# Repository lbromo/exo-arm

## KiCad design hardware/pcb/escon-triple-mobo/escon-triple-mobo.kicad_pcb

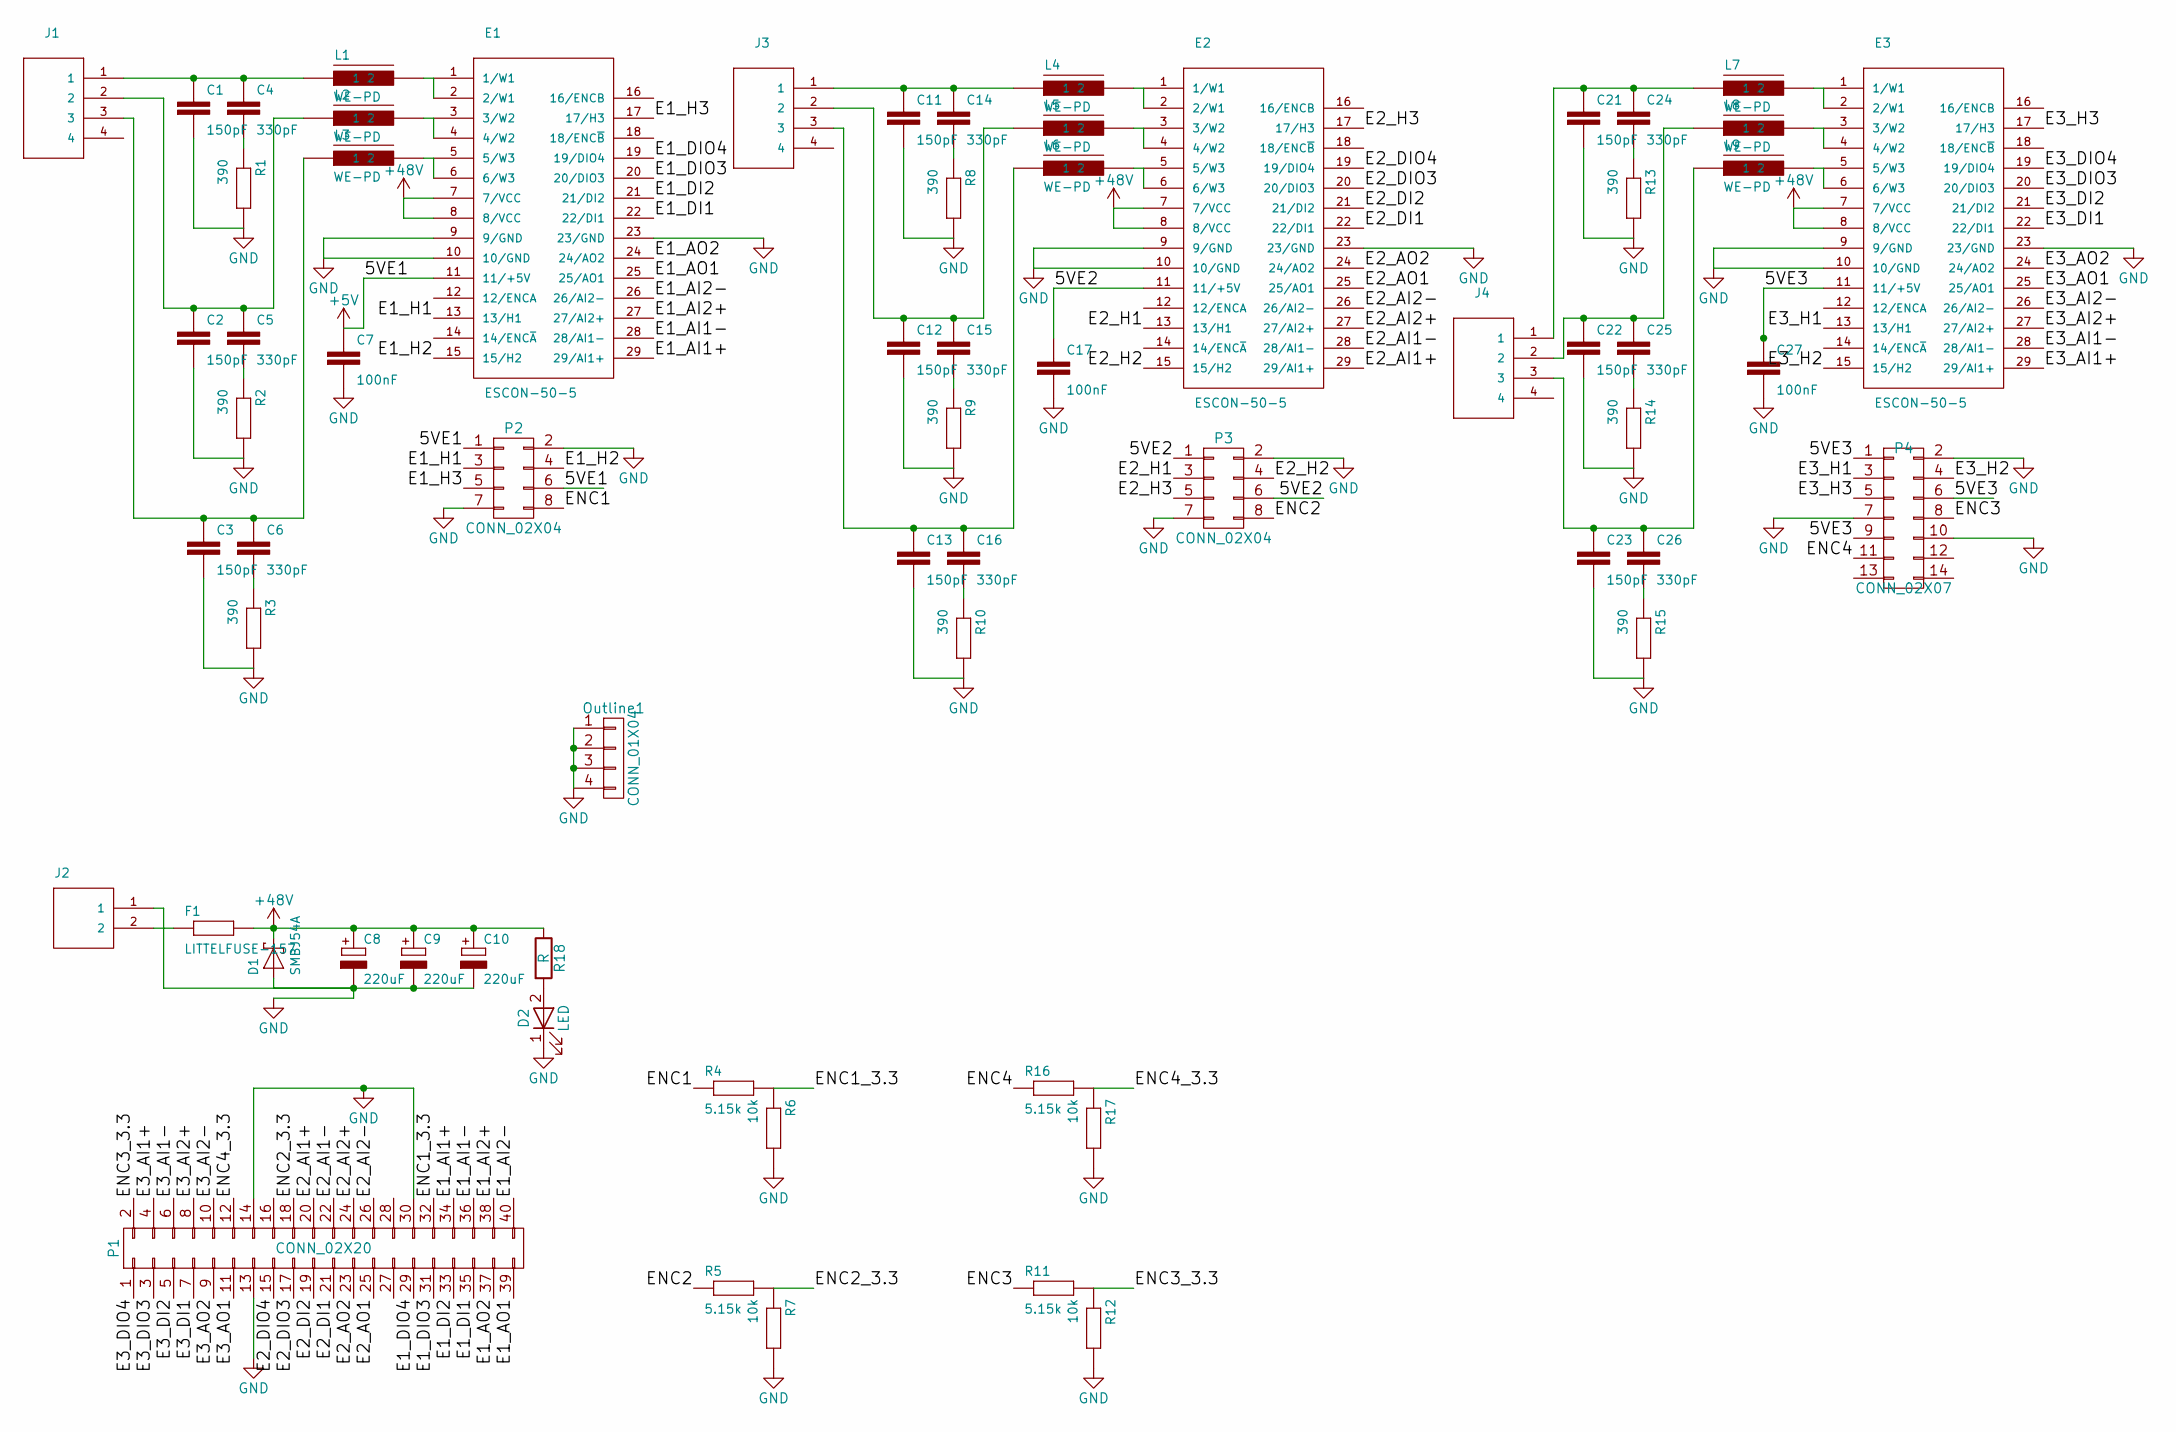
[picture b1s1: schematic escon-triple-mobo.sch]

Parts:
C1, C2, C3, C11, C12, C13, C21, C22, C23: 150pF; C_0805_HandSoldering
C4, C5, C6, C14, C15, C16, C24, C25, C26: 330pF; C_0805_HandSoldering
C7, C17, C27: 100nF; C_0805_HandSoldering
C8, C9, C10: 220uF; electrolyte-12-5
D1: SMBJ54A; SMB_Handsoldering
D2: LED; LED_0805
E1, E2, E3: ESCON-50-5; escon-50-5
F1: LITTELFUSE-157; Luttelfuse-157
J1, J3, J4: PHOENIX-COMBICON-MCV-4POS; PhoenixContact_MCV-G_04x3.50mm_Vertical
J2: PHOENIX-COMBICON-MCV-2POS; PhoenixContact_MCV-G_02x3.50mm_Vertical
L1, L2, L3, L4, L5, L6, L7, L8, L9: WE-PD; WE22uH
Outline1: CONN_01X04; EuroBoard160mmX100mm_holes
P1: CONN_02X20; IDC_Header_Straight_40pins
P2, P3: CONN_02X04; IDC_Header_Straight_8pins
P4: CONN_02X07; IDC_Header_Straight_14pins
R1, R2, R3, R8, R9, R10, R13, R14, R15: 390; R_0805_HandSoldering
R4, R5, R11, R16: 5.15k; R_0805_HandSoldering
R6, R7, R12, R17: 10k; R_0805_HandSoldering
R18: R; R_0805_HandSoldering

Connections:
+5V: C7.1, E1.11 (11/+5V), P2.1, P2.6
+48V: C8.1 (+), C9.1 (+), C10.1 (+), D1.2 (C), E1.7 (7/VCC), E1.8 (8/VCC), E2.7 (7/VCC), E2.8 (8/VCC), E3.7 (7/VCC), E3.8 (8/VCC), F1.2, R18.1
/5VE2: C17.1, E2.11 (11/+5V), P3.1, P3.6
/5VE3: C27.1, E3.11 (11/+5V), P4.1, P4.6, P4.9
/E1_AI1+: E1.29 (29/AI1+), P1.34
/E1_AI1-: E1.28 (28/AI1-), P1.36
/E1_AI2+: E1.27 (27/AI2+), P1.38
/E1_AI2-: E1.26 (26/AI2-), P1.40
/E1_AO1: E1.25 (25/AO1), P1.39
/E1_AO2: E1.24 (24/AO2), P1.37
/E1_DI1: E1.22 (22/DI1), P1.35
/E1_DI2: E1.21 (21/DI2), P1.33
/E1_DIO3: E1.20 (20/DIO3), P1.31
/E1_DIO4: E1.19 (19/DIO4), P1.29
/E1_H1: E1.13 (13/H1), P2.3
/E1_H2: E1.15 (15/H2), P2.4
/E1_H3: E1.17 (17/H3), P2.5
/E2_AI1+: E2.29 (29/AI1+), P1.20
/E2_AI1-: E2.28 (28/AI1-), P1.22
/E2_AI2+: E2.27 (27/AI2+), P1.24
/E2_AI2-: E2.26 (26/AI2-), P1.26
/E2_AO1: E2.25 (25/AO1), P1.25
/E2_AO2: E2.24 (24/AO2), P1.23
/E2_DI1: E2.22 (22/DI1), P1.21
/E2_DI2: E2.21 (21/DI2), P1.19
/E2_DIO3: E2.20 (20/DIO3), P1.17
/E2_DIO4: E2.19 (19/DIO4), P1.15
/E2_H1: E2.13 (13/H1), P3.3
/E2_H2: E2.15 (15/H2), P3.4
/E2_H3: E2.17 (17/H3), P3.5
/E3_AI1+: E3.29 (29/AI1+), P1.4
/E3_AI1-: E3.28 (28/AI1-), P1.6
/E3_AI2+: E3.27 (27/AI2+), P1.8
/E3_AI2-: E3.26 (26/AI2-), P1.10
/E3_AO1: E3.25 (25/AO1), P1.11
/E3_AO2: E3.24 (24/AO2), P1.9
/E3_DI1: E3.22 (22/DI1), P1.7
/E3_DI2: E3.21 (21/DI2), P1.5
/E3_DIO3: E3.20 (20/DIO3), P1.3
/E3_DIO4: E3.19 (19/DIO4), P1.1
/E3_H1: E3.13 (13/H1), P4.3
/E3_H2: E3.15 (15/H2), P4.4
/E3_H3: E3.17 (17/H3), P4.5
/ENC1: P2.8, R4.1
/ENC1_3.3: P1.32, R4.2, R6.1
/ENC2: P3.8, R5.1
/ENC2_3.3: P1.18, R5.2, R7.1
/ENC3: P4.8, R11.1
/ENC3_3.3: P1.2, R11.2, R12.1
/ENC4: P4.11, R16.1
/ENC4_3.3: P1.12, R16.2, R17.1
GND: C1.2, C2.2, C3.2, C7.2, C8.2 (-), C9.2 (-), C10.2 (-), C11.2, C12.2, C13.2, C17.2, C21.2, C22.2, C23.2, C27.2, D1.1 (A), D2.1 (K), E1.9 (9/GND), E1.10 (10/GND), E1.23 (23/GND), E2.9 (9/GND), E2.10 (10/GND), E2.23 (23/GND), E3.9 (9/GND), E3.10 (10/GND), E3.23 (23/GND), J2.1, Outline1.1, Outline1.2, Outline1.3, Outline1.4, P1.13, P1.14, P1.30, P2.2, P2.7, P3.2, P3.7, P4.2, P4.7, P4.10, R1.2, R2.2, R3.2, R6.2, R7.2, R8.2, R9.2, R10.2, R12.2, R13.2, R14.2, R15.2, R17.2
unnamed: C1.1, C4.1, J1.1, L1.1
unnamed: C2.1, C5.1, J1.2, L2.1
unnamed: C3.1, C6.1, J1.3, L3.1
unnamed: C4.2, R1.1
unnamed: C5.2, R2.1
unnamed: C6.2, R3.1
unnamed: C11.1, C14.1, J3.1, L4.1
unnamed: C12.1, C15.1, J3.2, L5.1
unnamed: C13.1, C16.1, J3.3, L6.1
unnamed: C14.2, R8.1
unnamed: C15.2, R9.1
unnamed: C16.2, R10.1
unnamed: C21.1, C24.1, J4.1, L7.1
unnamed: C22.1, C25.1, J4.2, L8.1
unnamed: C23.1, C26.1, J4.3, L9.1
unnamed: C24.2, R13.1
unnamed: C25.2, R14.1
unnamed: C26.2, R15.1
unnamed: D2.2 (A), R18.2
unnamed: E1.1 (1/W1), E1.2 (2/W1), L1.2
unnamed: E1.3 (3/W2), E1.4 (4/W2), L2.2
unnamed: E1.5 (5/W3), E1.6 (6/W3), L3.2
unnamed: E2.1 (1/W1), E2.2 (2/W1), L4.2
unnamed: E2.3 (3/W2), E2.4 (4/W2), L5.2
unnamed: E2.5 (5/W3), E2.6 (6/W3), L6.2
unnamed: E3.1 (1/W1), E3.2 (2/W1), L7.2
unnamed: E3.3 (3/W2), E3.4 (4/W2), L8.2
unnamed: E3.5 (5/W3), E3.6 (6/W3), L9.2
unnamed: F1.1, J2.2

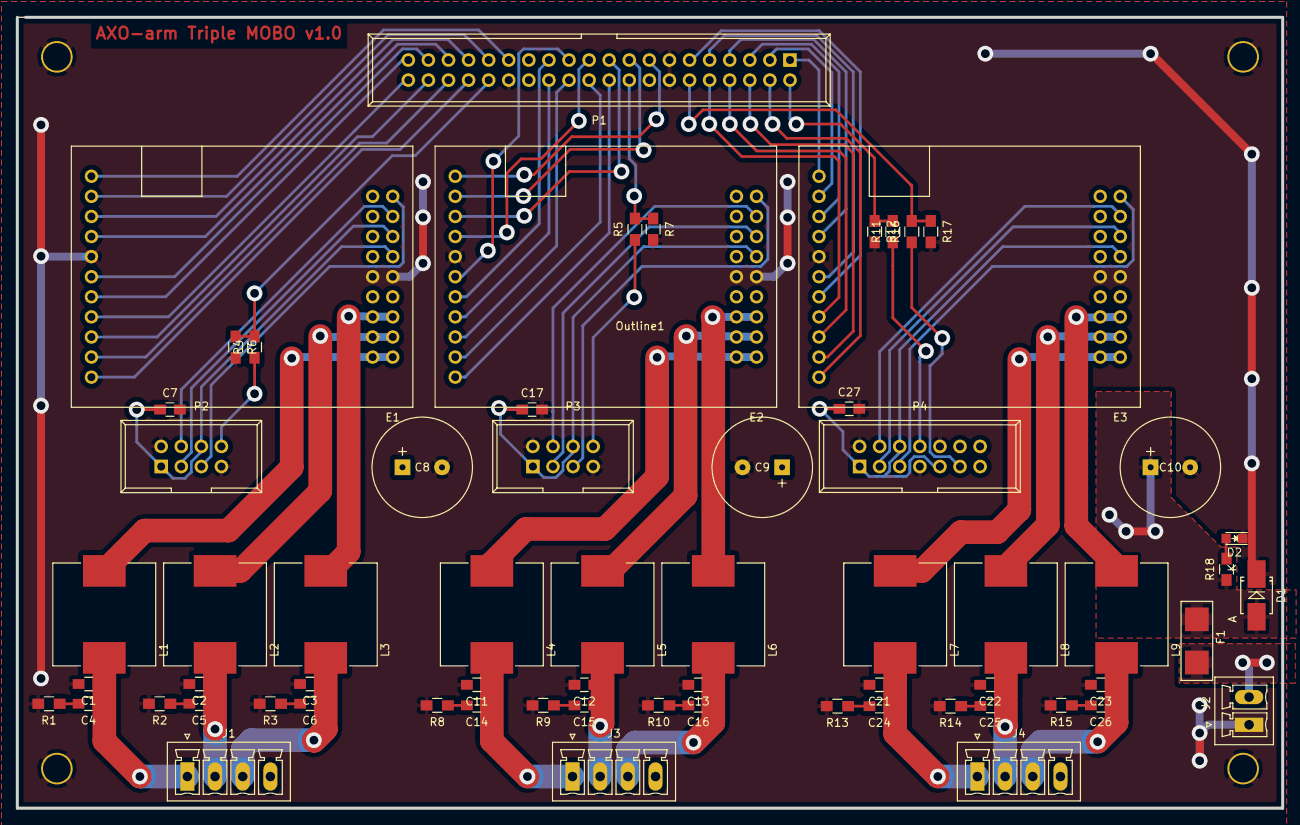
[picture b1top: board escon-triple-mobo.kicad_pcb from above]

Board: 2 copper layers, 160.0 x 100.0 mm, 66 parts (0 on the bottom side), 81 nets.

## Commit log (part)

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2016-11-03 debug
2016-11-03 removed som of the stupid prints
2016-11-03 added nice prints
2016-11-04 made a protocol that seems to work
2016-11-04 trying timeout for stuff
2016-11-04 debug leds
2016-11-04 arduino debug
2016-11-04 activity leds
2016-11-04 serial prot
2016-11-04 sequential program fro logging shiat
2016-11-04 got pritns under control
2016-11-04 faster samples
2016-11-04 just to ba able to push
2016-11-04 tests
2016-11-07 seq parest
2016-11-08 newest logging programs
2016-11-08 gb thingy
2016-11-10 Greybox thingy works
2016-11-10 additions to parest scripst
2016-11-10 file names
2016-11-10 good file names
2016-11-11 maybe plotting?
2016-11-11 angle measurements
2016-11-11 Added current and velocity
2016-11-11 no more plots
2016-11-11 added shoulder curr and vel
2016-11-11 we also want negativ vel
2016-11-17 initial hill model
2016-11-17 latest parest software stuff
2016-11-17 Stupid hill model
2016-11-17 some plots
2016-11-18 Hill based mucsle - doesnt blow up :)
2016-11-21 Clean up in matlab
2016-11-21 python implementaion of hill model
2016-11-21 muscle len python niceness
2016-11-21 new gitignore
2016-11-21 New new gitignore
2016-11-21 stufff
2016-11-21 momentarm
2016-11-21 angle->len->force
2016-11-21 removbed print
2016-11-21 added exception
2016-11-21 calculate torque estimate
2016-11-21 plotting nice stuff
2016-11-22 combined stuff
2016-11-22 plot to 140 degrees
2016-11-22 useful little scripts. add to matlab path for maximum awesomenes
2016-11-22 It is slow, but we have Minv, G and V matrix structure :D
2016-11-22 forgot to add :)
2016-11-22 Refactor: Moved symbolic matrice construction out of the class. The matrices are now stored in a file, and read from file instead of regeneration on every run. constant parameters are also subbed in 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
2016-11-22 added pip requirements
2016-11-23 fast simulation in python
2016-11-25 Added pcb to git
2016-11-26 finally working
2016-11-28 model is working
2016-11-28 new parameter estimation stuff
2016-11-28 removed not useful files
2016-11-28 activationsignal
2016-11-28 added missing argument in lambda function
2016-11-28 Python2 fixes
2016-11-28 added file for full simulation
2016-11-28 removed exe flag
2016-11-29 Changed emg freq. to 100 Hz
2016-11-30 all ze new parest stuff
2016-12-01 parameter estimation with the entire dataset
2016-12-07 added comments
2016-12-07 fixed issue with arguments for shoulder calculations
2016-12-07 played around with friction coeffs
2016-12-07 added ipython notebook with PSO estimation
2016-12-07 cleaned up ipython notebook
2016-12-07 testing with ipython notebooks
2016-12-07 PSO in a fair implementation
2016-12-07 comments in pso
2016-12-07 major cleanup
2016-12-11 added more parest scripts
2016-12-13 Added newest revision script
2016-12-21 Friction coeff's --- i think there is a sign error
2017-01-30 something something
2017-02-07 ignore .pyc files
2017-02-07 removed .pyc files
2017-02-07 moved requirements.txt to a more proper location
2017-02-07 model mech
2017-02-07 Delete InertiaCalculations.m
    Not used anymore
2017-02-07 had flipped the motor interia (it was on the wrong joints)
2017-02-07 mech arm der nu virker i matlab- Wuhuuu
2017-02-07 new plots
2017-02-07 added emg filter stuff
2017-02-08 implemented EMG filtering
2017-02-08 at bit prettier
2017-02-08 nyt til muskelmodel
2017-02-09 muscle
2017-02-09 removed outputs
2017-02-09 using the bicect algorithm from scipy to find dLce and dLse numerically
    Lower tolerence of the on the online bisection calculations -- runs 4 times faster
2017-02-09 stripped output from ipython notebooks
2017-02-09 angles > 180 doesnt really make sense
2017-02-09 dont track ipynb_checkpoints
2017-02-13 observer pattern for activation signals
2017-02-13 new eagle file
2017-02-13 new useful scripts
2017-02-13 added files deleted by acident
2017-02-13 added files deleted by accident
2017-02-13 several_tests
2017-02-13 added a random width step function
2017-02-13 Now with random squares and sine sweep
2017-02-15 Now outputs loads of shit
2017-02-16 MORE LOGS!
2017-02-16 All mortens latest shit
2017-02-20 mat files with parameters
2017-02-20 modified logs
2017-02-21 mortens latest and greatest parest
2017-02-21 parest cleanup
2017-02-21 mat model
2017-02-21 both
2017-02-21 slight mods to model. Nothing serious
2017-02-21 added space for udoo software
2017-02-22 model
2017-02-22 ARRRG!
2017-02-22 updated angle cal
2017-02-23 FAILED
2017-02-23 added more logs
2017-02-27 try: excpet: around the bisect call.. If it fails we will assume that dLpe = dLce
2017-02-27 added an exploratory notebook where PyGMO fits parameters to muscle(s)
2017-02-28 parest stuff
2017-02-28 mortens updates
2017-02-28 nice little script for pwm 2 current conversion
2017-03-01 Now without scaling minimum owm
2017-03-01 LOGS!
2017-03-01 Morten attempted feedback linearization. Currently going to shit
2017-03-02 Mortens Simulator
2017-03-02 made folder for controllers
2017-03-03 mortens awesome feedback linearized controlelr
2017-03-06 NEW MSE SCRIPT
2017-03-06 hejssa
2017-03-06 now with goodnessOfFit()
2017-03-06 mortens controller experiments
2017-03-07 now using NMSE
2017-03-07 added some log files
2017-03-08 ØVVV!
2017-03-09 angle_input
2017-03-09 updated arduino control sketch, messenger now with ref
2017-03-10 rougth position estimate
2017-03-10 changed pin
2017-03-10 updated conversion for udoo
2017-03-10 morten solved overflowing int
2017-03-10 all mortens silly corrections
2017-03-13 Newest UDOO software. Now without truncating everything
2017-03-13 seperate stuff
2017-03-14 added matrix multiplication and matrix vector multiplication
2017-03-14 renaming and splitting out
2017-03-14 moved shit around
2017-03-14 updated stuff
2017-03-14 All the shit
2017-03-14 Simulation niceness.. Now with both mex, matlab and Arduino in the loopgst
2017-03-14 New matrix math and controller awesomeness
2017-03-14 corrections. New .gitignore
2017-03-14 fixed operator errors
2017-03-14 comments
2017-03-14 Revert "comments". Didn't mean to commit it :)
    This reverts commit dbe077652c2a9d1ac5fc3168e6478decebcc7e02.
2017-03-14 moved vector operators up the rest of the vector ctors
2017-03-15 Readded Matrixmath
2017-03-15 added copy ctor and assignment operator for matrices
2017-03-15 Default value for x0 and ref in exo_sim, messing around with def and ifndef, updated arduino_part to use Lasses c++ controller
2017-03-15 removed mat files, updated .gitignore to leave out symlinks
2017-03-16 Added admittance controller
2017-03-17 Added newest controller mods. Now with controller parameter struct. Also commented out some stuff in Matrix.cpp
2017-03-20 Latest changes to udoo
2017-03-20 Copy constructor and assignment operator is working on arduino
2017-03-20 output vector 'u' as a global variable
2017-03-21 Removed ktN from cur signal
2017-03-21 use afs
2017-03-21 added missing files
2017-03-22 I think I found out what is wrong. We need to multiply with 1/ktN
2017-03-23 cd into parest dir
2017-03-23 awesome
2017-03-23 save mse in the pickle
2017-03-23 fixed values
2017-03-23 stuff
2017-03-23 extract imu measurements
2017-03-23 fixed issue where the angle was ćut off too early of the last ext test
2017-03-23 fixed wrong angles stuff in mmre1.py
2017-03-23 maybe ready for parest
2017-03-24 Added the new pcb to git
2017-03-25 fixed for loop
2017-03-27 better?
2017-03-27 whoops
2017-03-27 megs
2017-03-27 added newest kicad
2017-03-27 small script for getting measurements into matlab
2017-03-27 fixed naming thing
2017-03-27 added stuff
2017-03-29 updated to run with 100 particles
2017-03-29 New N matrix! Also, added some compiler flags for things..
2017-03-30 1k 2 muscles
2017-04-05 first attempt at admittance control.. Simulation looks fine
2017-04-07 small changes in hardware files. Prolly just metadata. Updated parameter estimation scripts
2017-04-10 tested the pcb, made new parest meas. Everything seemed fine
2017-04-10 muscle model parameter verification
2017-04-17 Added an admittance filter thingy
2017-04-17 The UDOO software should be working now. Periodic control implemented with HWTIMERga model/useful_scripts/makeFIR.m!
2017-04-17 added python impl of an admittance PID filter
2017-04-17 added a wrapper function to create muscles based on a dict with paramters
2017-04-17 small script to cleanup the parest dicts
2017-04-17 ignore dat files
2017-04-17 Couldn't figure out how to 'live plot' with python3, so instead we broadcast the state vector over a udp socket, and the plotter scipt just plots from that state vector
2017-04-17 uhm. dunno
2017-04-17 2 muslce pickles
2017-04-17 updated mech model
2017-04-17 updated the full simulation
2017-04-17 removed all the stuff I accidentally added. I think
2017-04-17 made logging nice
2017-04-18 new controller
2017-04-19 moved arduino specific stuff out in hal
2017-04-19 1st attempt
2017-04-20 delayed matplotlib import
2017-04-20 pymyo can be installed with distutils -- no need to add it in path
2017-04-20 Serial stuff was really slow -- it is now in a Timer running each 0.01 second, and we just use the newest value when estimation joint torque
2017-04-20 100 hz sampling instead of 200
2017-04-20 moved default log decleration to a more appropiate place
2017-04-20 made some log files same length
2017-04-20 Mortens sim test script
2017-04-20 test fuck
2017-04-20 modified n vector to use correct model
2017-04-20 better
2017-04-20 verify with 2 muslces
2017-04-20 modified load_data
2017-04-21 added act signal to dat files for 4 muscles parest
2017-04-21 added act signal to dat files for 2 muscles parest
2017-04-21 added missing comma
2017-04-21 add emg to dat file, and print MSE
2017-04-21 added notebook to generate data file for estimatin chap with 4 muscles
2017-04-21 added notebook to generate data file for estimatin chap with 2 muscles
2017-04-21 changed data file name
2017-04-21 use space instead of a mixture of space and comma to seperate, and clean up headers
2017-04-25 controller sim script.. Is fairly shitty
2017-04-25 Revert "Maybe I fixed the angle"
    You didn't :) - This reverts commit 5307cb7b142d6fbd2eb06e49420e4862634ec03c.
2017-04-26 added stupid test as part of debugging the serial interface on the arduino
2017-04-26 appened state vector to include i_theta_s and i_theta_e
2017-04-26 T_SAMPLE_S should be a floating point number
2017-04-26 Fucking working
2017-04-26 Fixed an error where the copy constructor freed the memory of the original, invalidating the original
2017-04-26 use the old new N vector
2017-04-26 removed old junk
2017-04-26 ignore pickles
2017-04-26 cleanup and comments
2017-04-26 added functionality for minimal jerk
2017-04-26 changed ref print
2017-04-26 added log file for Lasse
2017-04-26 made better minjerk
2017-04-27 exo_sim now uses the reference in minjerk.csv
2017-04-27 I think I made PID correctly. Maybe we should add anti-windup
2017-04-27 Maybe the position is nice and fixed
2017-04-27 newest arduino sketch, works well
2017-04-27 newest messenger capable of using predefined path
2017-04-28 modification of exo_sim
2017-04-28 we need the M4 faster than the A9
2017-04-28 can now do 100 Hz
2017-04-28 faster logging -- using file as queue xD
2017-04-28 moved stuff around abit
2017-04-28 soft max on 90 deg
2017-04-28 added logs
2017-05-01 create a emg logger when ww are running
2017-05-01 made log files same length
2017-05-08 uses real angles ala mortens idea
2017-05-08 just notebooks
2017-05-10 admittance filter
2017-05-10 added new parametersscript that shold fit with model. I think
2017-05-10 Updated system matrices with 320mm link len
2017-05-10 changed link len to 320mm and removed an N
2017-05-10 negativ angles hack and updated admittance values
2017-05-10 we moved the arm a little
2017-05-11 add time to the emg logs
2017-05-17 more loggging
2017-05-17 rapport gains
2017-05-19 Made new n vector without gravity compensation
2017-05-19 I think the elbow should work now :)
2017-05-22 formatting
2017-05-22 use the normal controller
2017-05-23 update from monday
2017-05-29 updated so pagmo doesnt crash
2017-05-29 folder structure
2017-05-30 better logging
2017-06-12 increased resolution of reference
